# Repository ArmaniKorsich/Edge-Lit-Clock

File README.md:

# Edge Lit Clock

An Atmega328p powered clock using acryllic panels and ws2812b addressable LEDs as displays.
#

## CAD

All drawings created in Inventor 2016.

The clock consists of 5 seperate displays chained together, with:
* 3
* 10
* 6
* 10
* 6*

panels each. Each panel has a number from 0-9 etched in the following order:  

The off order resembles the old Nixie tube number ordering meant to maximize visiblity of all the digits.

\* *The last display has various symbols instead:*  

## Electronics

The Atmega328p drives the WS2812B leds using the eLite and FastLED libraries.

The Atmega328p reads time from a DS32321 RTC.  

To protect time information against power outages, I selected a DS3231 which accepts backup battery voltage on PIN14 in the event that VCC cuts out.

All circuit boards were constructed on 2 layer PCBs.
The circuit boards were manufactured by JLCPCB and designed using Autodesk Eagle.

### Input

The device takes 9-40VDC input with at least 2A current capacity. The LM2575-5V buck converter transforms the input to 5V with a 3A limit.

The average current draw of the Edge Lit CLock is ~350 mA with an average of 16 WS2812B activated at any moment.

### Operation

To turn the device on, set the 'POWERTOGGLE' piano switch on the bottom right of the PCB to the 'DOWN' position.

To turn the alarm on, set the 'ALARMTOGGLE' piano switch to the 'DOWN' position.

The three potentiometers on the device control the RED, GREEN, and BLUE color channels of the LEDs.

Pressing the Photoresist_Set button will toggle tracking ambient brightness. When set, the device will lower the brightness of its LEDs to 20% in a fully dark room.

### Setting a Timer

To set a timer, press the TIMER+ or TIMER- button until the device displays the appropriate countdown time.

To start the timer, pres the TIMER_SET button. The device will begin counting down from the set time.

For countdowns over 30 minutes, the device will display hours on the 2 left displays, and minutes on the 2 right displays.

When the countdown reaches <30 minutes, the device will display minutes on the 2 left displays, and seconds on the 2 right displays.

When the countdown reaches 0 seconds, a buzzer will beep.

To disable the buzzing, press the SNOOZE button or restart the device.

## Schematics

## Source

This project takes advantage of Arduino's public library system, using 
stdio, FastLED ResponsiveAnalaogRead, EEPROM, Wire, RTCLib
and the provided eLite library for controlling the displays.

ResponsiveAnalogRead: Provides fast and mathematically continuous input values. Minimizes noise in low-cost potentiometers.

stdio: Optional, provides useful debugging information in Arduino IDE.

FastLED: A solution to controlling a large quantity of LEDs rapidly and arbitrarily.

RTClib: Interfaces with the DS3231 Real Time Clock, functions for timekeeping.  

## eLite Library

The eLite library represents the bulk of the content of this project, the clock and physical shape of the project are an example applying this library as my entry to Eisenhower Senior High School's 'Yearly Engineering and Innovation Design Scholarship.'    

`uint8_t defineChain(uint8_t numDisplays,...);`. 
> Inputs(NumDisplays): Number of chained displays in the system.    
> return(chainLength): returns the number of displays in the system.

`void defineLedPerPanel(uint8_t led,...);`. 
> Inputs(led): How many displays there are  
> Inputs(,...): The number of leds per panel in a display, seperated by commas.  
> Tells the system how many LEDs each display has. Useful with physically large plexiglass panels that need more lighting.  
> For a system with 5 displays and 2 leds per panel on each display:  
`void defineLedPerPanel(5, 2, 2, 2, 2, 2)`. 

`void setStandardOrder(uint8_t displayToConfigure);`. 
> inputs(displayToConfigure): Which display to configure. 
> Resets the numercal order of panels in a given display to 0, 1, 2, ... , n. 

`void redefinePanelOrder(uint8_t displayToConfigure, uint8_t quantityPanels,...);`. 
> Inputs(displayToConfigure): Which display to configure   
> Inputs(QuantityPanels): Quantity of panels in display 'DisplayToConfigure'   
> Inputs(,...): The custom order of panels in the display, expects 'QuantityPanels' items, seperated by commas.  

`void drawPanel(uint8_t r, uint8_t g, uint8_t b, uint8_t displayCount, int panelToDraw);`. 
> Inputs(R, G, B): 8-bit integer (0-255), sets the primary color of the displays.     
> Inputs(displayCount): Which display to draw to.  
> Inputs(panelToDraw): The panel to activate in color ##RRGGBB   

`void drawChain(uint8_t r, uint8_t g, uint8_t b, uint8_t lengthOfChain,...);`. 
> Inputs(R, G< B): 8-bit integer (0-255), sets the primary color of the displays.  
> Inputs(lengthOfChain): Number of displays to activate in the chain (0-indexed).  
> inputs(,...): The panel number to activate in each display, seperated by commas.   

`void cycleDisplays(int delayTime, int acceleration, bool direc, uint8_t r, uint8_t g, uint8_t b, uint8_t qtyToCycle,...);`. 
> Inputs(delayTime): Pause between advancing the panels (mS).  
> Inputs(acceleration): Time to decrese delayTime by after each iteration. (mS).  
> Inputs(direc): Cycles forwards (1) or backwards (0).   
> Inputs(R, G, B): 8-bit integer (0-255), sets the primary color of the displays.   
> Inputs(qtyToCycle): Number of displays in the chain to cycle through.   
> Inputs(,...): The index of the displays you wish to cycle through.  
> In a chain of 5 displays, if we wish to cycle the 1st, 3rd, and 4th display:  
`void cycleDisplays(delay, acceleration, forward, R, G, B, 3, 0, 2, 3)`.

`void clearDisplay(uint8_t displayToClear);`
> Inputs(displayToClear): Which display to clear, all panels will be deactivated.  

`void clearChain();`
> Turns off all LEDs in the system, clears all displays.

`uint8_t setChainBrightness(uint8_t brightness);`
> Inputs(brightness): 8-bit integer (0-255), sets the overall opacity (brightness) of the LEDs in FastLED.
> return(brightnessLevel): returns the brightness of the LEDs.

`void randomizeDisplays(int delayTime, int acceleration, int iterations, uint8_t r, uint8_t g, uint8_t b, uint8_t qtyToRandomize, ...);`
> Inputs(delayTime): Pause between iterations in milliseconds (mS).    
> Inputs(acceleration): Time to decrease delayTime by after each iteration. (mS).   
> Inputs(iterations): How many times to activate a random panel on the given displays.    
> Inputs(R, G, B): 8-bit integer (0-255), sets the primary color of the displays.   
> Inputs(qtyToRandomize): Number of displays in the chain to randomize.  
> Inputs(,...): The index of the displays you wish to randomize.  
> If iterations is 1, delay and acceleration aren't important, as the given displays will simply output a random panel. Otherwise, this function provides a simple animation to your chain.

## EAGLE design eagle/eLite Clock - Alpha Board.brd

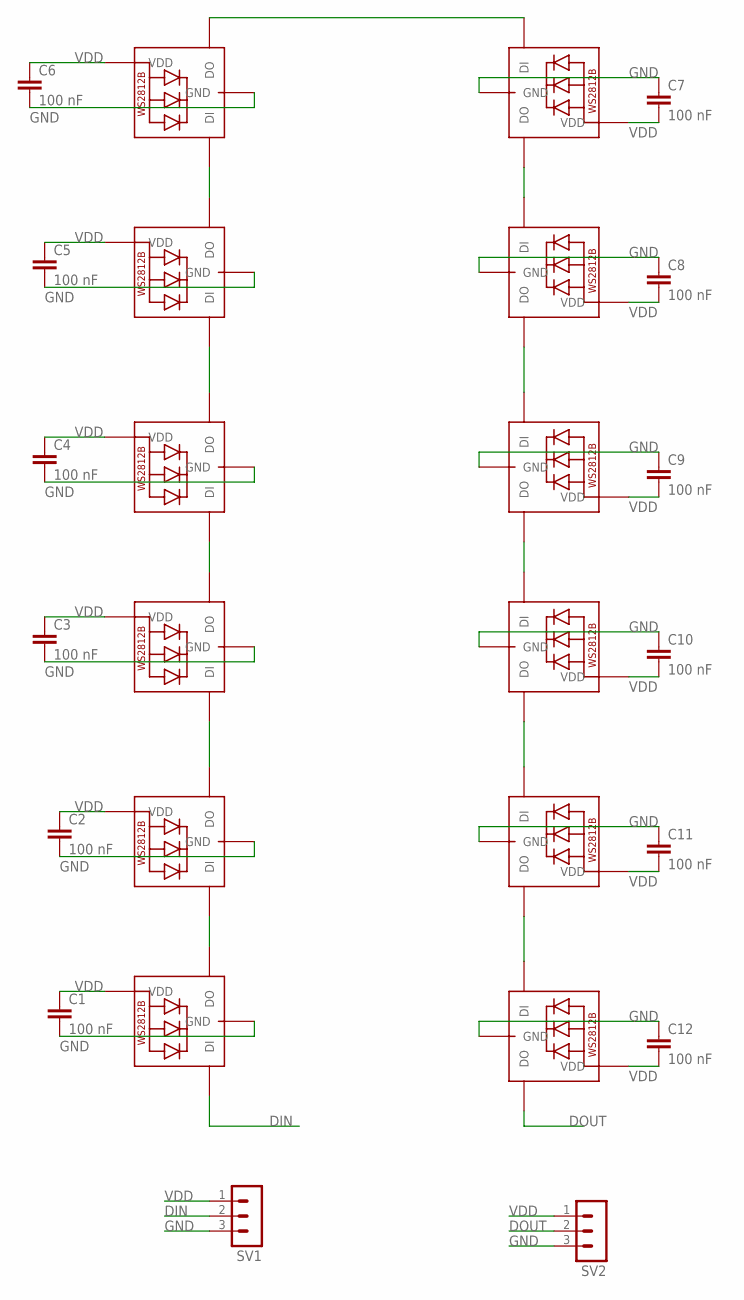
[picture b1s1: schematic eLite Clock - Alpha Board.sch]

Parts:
C1, C2, C3, C4, C5, C6, C7, C8, C9, C10, C11, C12: 100 nF; C025-025X050
LED1, LED2, LED3, LED4, LED5, LED6, LED7, LED8, LED9, LED10, LED11, LED12: WS2812B_5050W; WS2812B-WIDE
SV1, SV2: MA03-1

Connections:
DIN: LED1.4-DIN (DI), SV1.2
DOUT: LED12.2-DOUT (DO), SV2.2
GND: C1.2, C2.2, C3.2, C4.2, C5.2, C6.2, C7.1, C8.1, C9.1, C10.1, C11.1, C12.1, LED1.3-GND (GND), LED2.3-GND (GND), LED3.3-GND (GND), LED4.3-GND (GND), LED5.3-GND (GND), LED6.3-GND (GND), LED7.3-GND (GND), LED8.3-GND (GND), LED9.3-GND (GND), LED10.3-GND (GND), LED11.3-GND (GND), LED12.3-GND (GND), SV1.3, SV2.3
unnamed: LED1.2-DOUT (DO), LED2.4-DIN (DI)
unnamed: LED2.2-DOUT (DO), LED3.4-DIN (DI)
unnamed: LED3.2-DOUT (DO), LED4.4-DIN (DI)
unnamed: LED4.2-DOUT (DO), LED5.4-DIN (DI)
unnamed: LED5.2-DOUT (DO), LED6.4-DIN (DI)
unnamed: LED6.2-DOUT (DO), LED7.4-DIN (DI)
unnamed: LED7.2-DOUT (DO), LED8.4-DIN (DI)
unnamed: LED8.2-DOUT (DO), LED9.4-DIN (DI)
unnamed: LED9.2-DOUT (DO), LED10.4-DIN (DI)
unnamed: LED10.2-DOUT (DO), LED11.4-DIN (DI)
unnamed: LED11.2-DOUT (DO), LED12.4-DIN (DI)
VDD: C1.1, C2.1, C3.1, C4.1, C5.1, C6.1, C7.2, C8.2, C9.2, C10.2, C11.2, C12.2, LED1.1-VDD (VDD), LED2.1-VDD (VDD), LED3.1-VDD (VDD), LED4.1-VDD (VDD), LED5.1-VDD (VDD), LED6.1-VDD (VDD), LED7.1-VDD (VDD), LED8.1-VDD (VDD), LED9.1-VDD (VDD), LED10.1-VDD (VDD), LED11.1-VDD (VDD), LED12.1-VDD (VDD), SV1.1, SV2.1

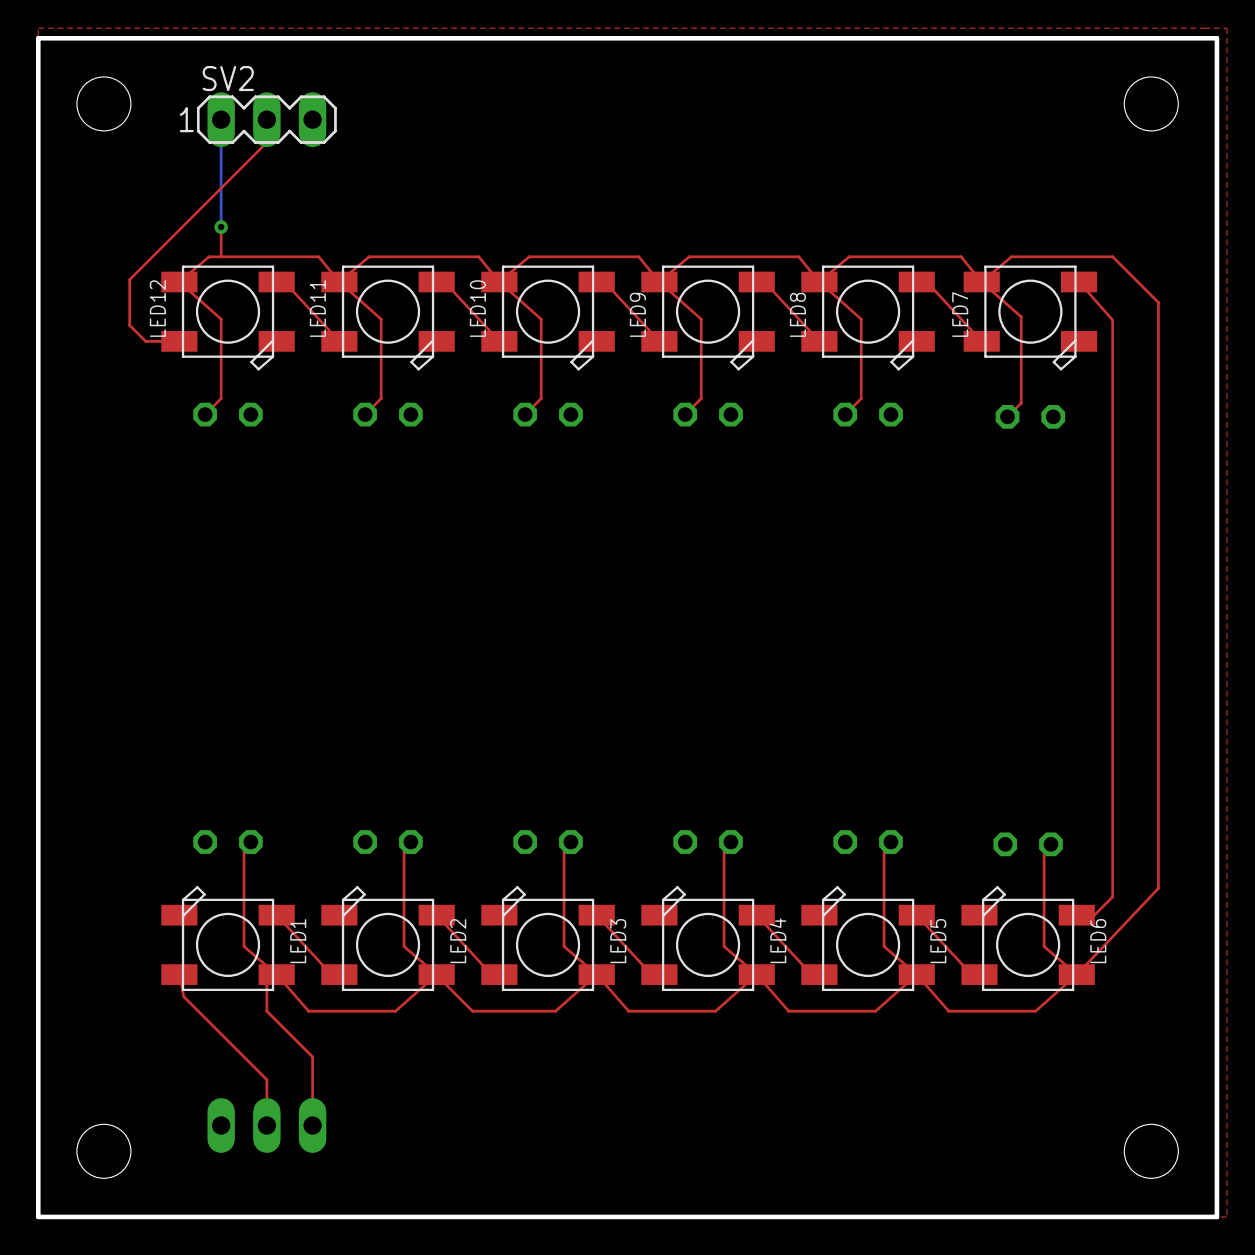
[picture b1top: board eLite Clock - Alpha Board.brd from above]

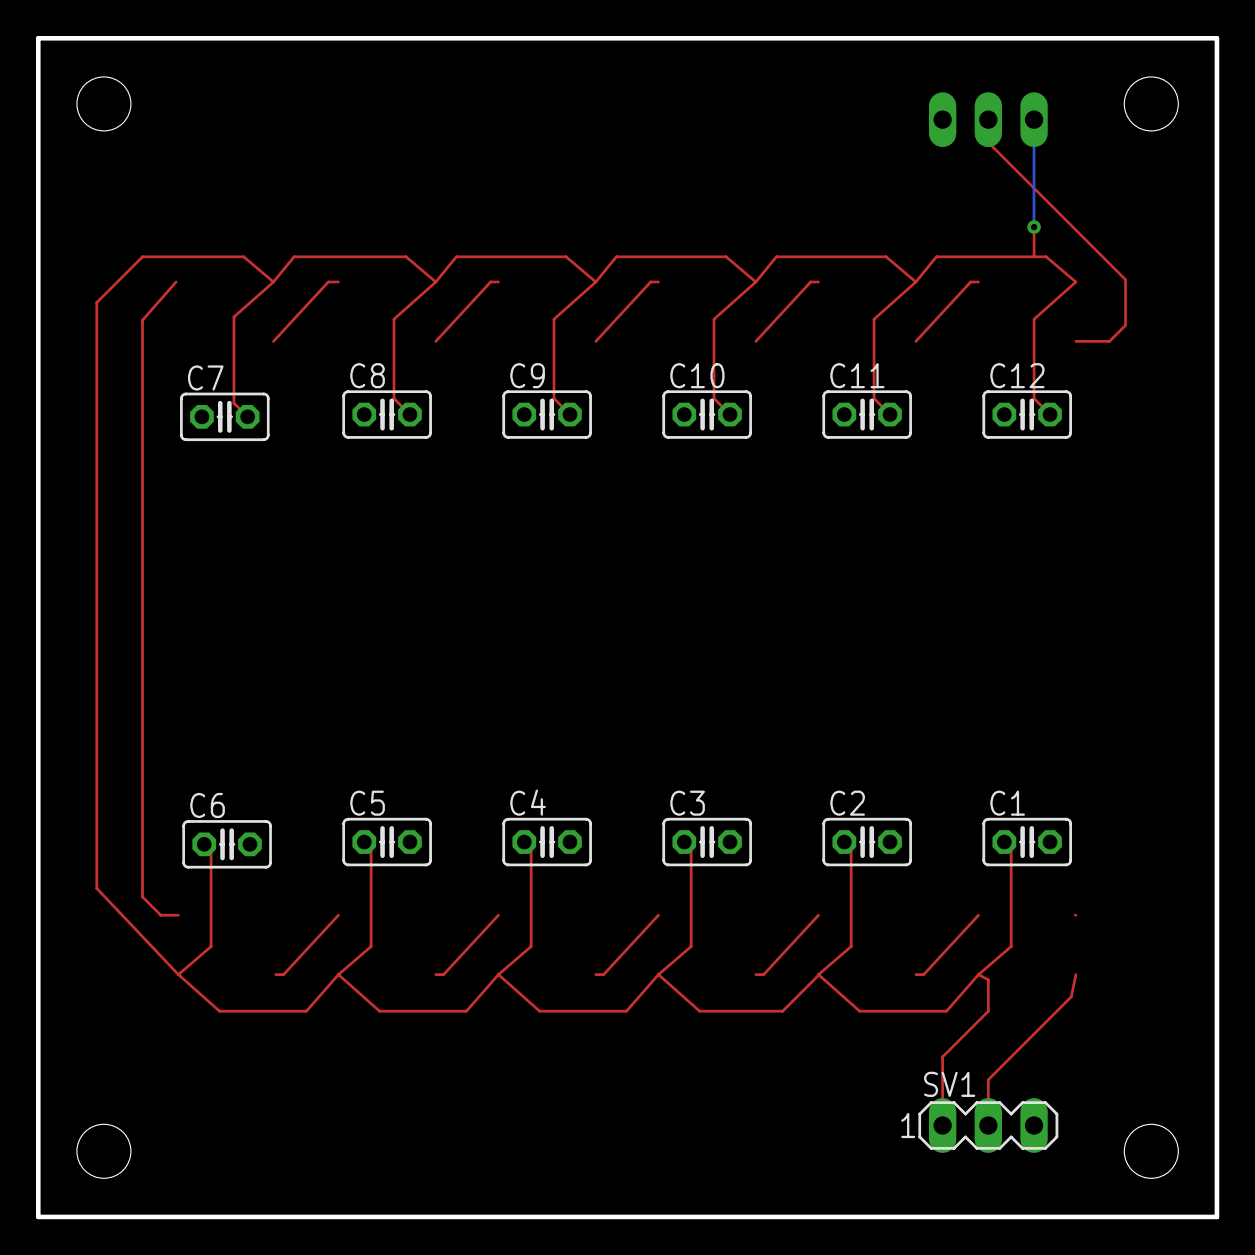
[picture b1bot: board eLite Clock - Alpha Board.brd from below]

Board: 2 copper layers, 65.5 x 65.5 mm, 26 parts (13 on the bottom side), 15 nets.

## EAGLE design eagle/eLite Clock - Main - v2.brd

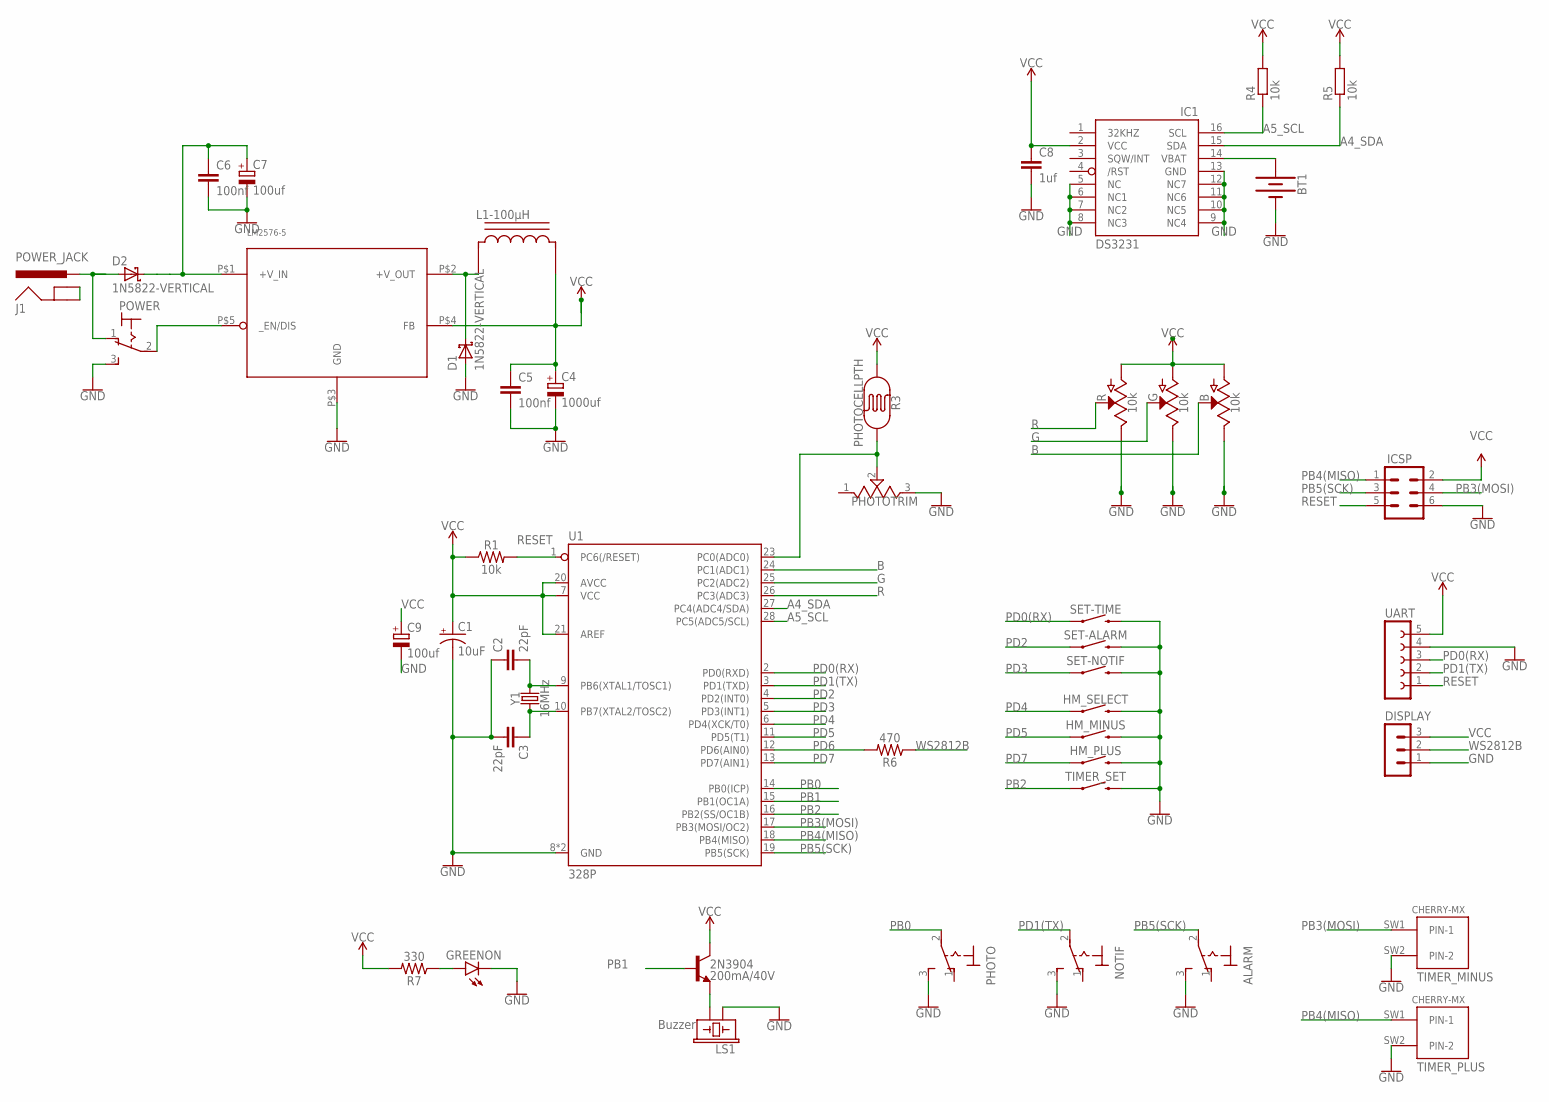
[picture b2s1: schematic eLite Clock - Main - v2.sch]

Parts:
2N3904: 200mA/40V; TO-92
ALARM: 320-916
B: 10k; SINGLE_GANK_POTENTIOMETER
BT1: BATTERY-20MM_PTH; BATTCOM_20MM_PTH
C1: 10uF; CPOL-RADIAL-2.5MM-5MM
C2, C3: 22pF; CAP-PTH-2.54
C4: 1000uf; E5-13
C5, C6: 100nf; C025-025X050
C7: 100uf; E2,5-5
C8: 1uf; C025-025X050
C9: 100uf; E3,5-10
D1, D2: 1N5822-VERTICAL; DIODE-VERTICAL
DISPLAY: MA03-1
G: 10k; SINGLE_GANK_POTENTIOMETER
GREENON: LED5MM
HM_MINUS: MOMENTARY-SWITCH-SPST-PTH-6.0MM; TACTILE_SWITCH_PTH_6.0MM
HM_PLUS: MOMENTARY-SWITCH-SPST-PTH-6.0MM; TACTILE_SWITCH_PTH_6.0MM
HM_SELECT: MOMENTARY-SWITCH-SPST-PTH-6.0MM; TACTILE_SWITCH_PTH_6.0MM
IC1: DS3231/SO; SO16W
ICSP: MA03-2
J1: POWER_JACK; POWER_JACK_PTH
L1-100µH: T37_INDUCTOR
LM2576-5: LM2576-T05A; TO-220-5_IN-LINE
LS1: Buzzer; BUZZER-12MM
NOTIF: 320-916
PHOTO: 320-916
PHOTOTRIM: 3306F-1-203; TRIM_3306F-1-203
POWER: 320-916
R: 10k; SINGLE_GANK_POTENTIOMETER
R1: 10k; AXIAL-0.3
R3: PHOTOCELLPTH; PHOTOCELL
R4, R5: 10k; 0207/7
R6: 470; AXIAL-0.3
R7: 330; AXIAL-0.3
SET-ALARM: MOMENTARY-SWITCH-SPST-PTH-6.0MM; TACTILE_SWITCH_PTH_6.0MM
SET-NOTIF: MOMENTARY-SWITCH-SPST-PTH-6.0MM; TACTILE_SWITCH_PTH_6.0MM
SET-TIME: MOMENTARY-SWITCH-SPST-PTH-6.0MM; TACTILE_SWITCH_PTH_6.0MM
TIMER_MINUS: TIMER_PLUS; CHERRY-MX
TIMER_PLUS: TIMER_MINUS; CHERRY-MX
TIMER_SET: MOMENTARY-SWITCH-SPST-PTH-6.0MM; TACTILE_SWITCH_PTH_6.0MM
U1: 328P; DIP28
UART: FE05-1
Y1: 16MHz; HC49US

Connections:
A4_SDA: IC1.15 (SDA), R5.1, U1.27 (PC4(ADC4/SDA))
A5_SCL: IC1.16 (SCL), R4.1, U1.28 (PC5(ADC5/SCL))
B: B.P$2, U1.24 (PC1(ADC1))
G: G.P$2, U1.25 (PC2(ADC2))
GND: ALARM.3 (S), B.P$1, BT1.2 (-), C1.2 (-), C2.1, C3.2, C4.-, C5.2, C6.2, C7.-, C8.2, C9.-, D1.ANODE (A), DISPLAY.1, G.P$1, GREENON.K (C), HM_MINUS.3 (2), HM_PLUS.3 (2), HM_SELECT.3 (2), IC1.5 (NC), IC1.6 (NC1), IC1.7 (NC2), IC1.8 (NC3), IC1.9 (NC4), IC1.10 (NC5), IC1.11 (NC6), IC1.12 (NC7), IC1.13 (GND), ICSP.6, LM2576-5.P$3 (GND), LS1.+ (1), NOTIF.3 (S), PHOTO.3 (S), PHOTOTRIM.3 (CW), POWER.3 (S), R.P$1, SET-ALARM.3 (2), SET-NOTIF.3 (2), SET-TIME.3 (2), TIMER_MINUS.SW2 (PIN-2), TIMER_PLUS.SW2 (PIN-2), TIMER_SET.3 (2), U1.8 (GND), U1.22 (GND), UART.4
unnamed: J1.GND, J1.GNDBREAK
unnamed: C2.2, U1.9 (PB6(XTAL1/TOSC1)), Y1.2
unnamed: C3.1, U1.10 (PB7(XTAL2/TOSC2)), Y1.1
unnamed: GREENON.A, R7.P$1 (1)
unnamed: PHOTOTRIM.2 (W), R3.2, U1.23 (PC0(ADC0))
unnamed: D2.ANODE (A), J1.PWR, POWER.1 (O)
unnamed: LM2576-5.P$5 (_EN/DIS), POWER.2
unnamed: 2N3904.1 (E), LS1.- (2)
unnamed: D1.CATHODE (C), L1-100µH.CB, LM2576-5.P$2 (+V_OUT)
unnamed: C6.1, C7.+, D2.CATHODE (C), LM2576-5.P$1 (+V_IN)
unnamed: BT1.1 (+), IC1.14 (VBAT)
PB0: PHOTO.2, U1.14 (PB0(ICP))
PB1: 2N3904.2 (B), U1.15 (PB1(OC1A))
PB2: TIMER_SET.1, U1.16 (PB2(SS/OC1B))
PB3(MOSI): ICSP.4, TIMER_MINUS.SW1 (PIN-1), U1.17 (PB3(MOSI/OC2))
PB4(MISO): ICSP.1, TIMER_PLUS.SW1 (PIN-1), U1.18 (PB4(MISO))
PB5(SCK): ALARM.2, ICSP.3, U1.19 (PB5(SCK))
PD0(RX): SET-TIME.1, U1.2 (PD0(RXD)), UART.3
PD1(TX): NOTIF.2, U1.3 (PD1(TXD)), UART.2
PD2: SET-ALARM.1, U1.4 (PD2(INT0))
PD3: SET-NOTIF.1, U1.5 (PD3(INT1))
PD4: HM_SELECT.1, U1.6 (PD4(XCK/T0))
PD5: HM_MINUS.1, U1.11 (PD5(T1))
PD6: R6.P$2 (2), U1.12 (PD6(AIN0))
PD7: HM_PLUS.1, U1.13 (PD7(AIN1))
R: R.P$2, U1.26 (PC3(ADC3))
RESET: ICSP.5, R1.P$2 (2), U1.1 (PC6(/RESET)), UART.1
VCC: 2N3904.3 (C), B.P$3, C1.1 (+), C4.+, C5.1, C8.1, C9.+, DISPLAY.3, G.P$3, IC1.2 (VCC), ICSP.2, L1-100µH.CA, LM2576-5.P$4 (FB), R.P$3, R1.P$1 (1), R3.1, R4.2, R5.2, R7.P$2 (2), U1.7 (VCC), U1.20 (AVCC), U1.21 (AREF), UART.5
WS2812B: DISPLAY.2, R6.P$1 (1)

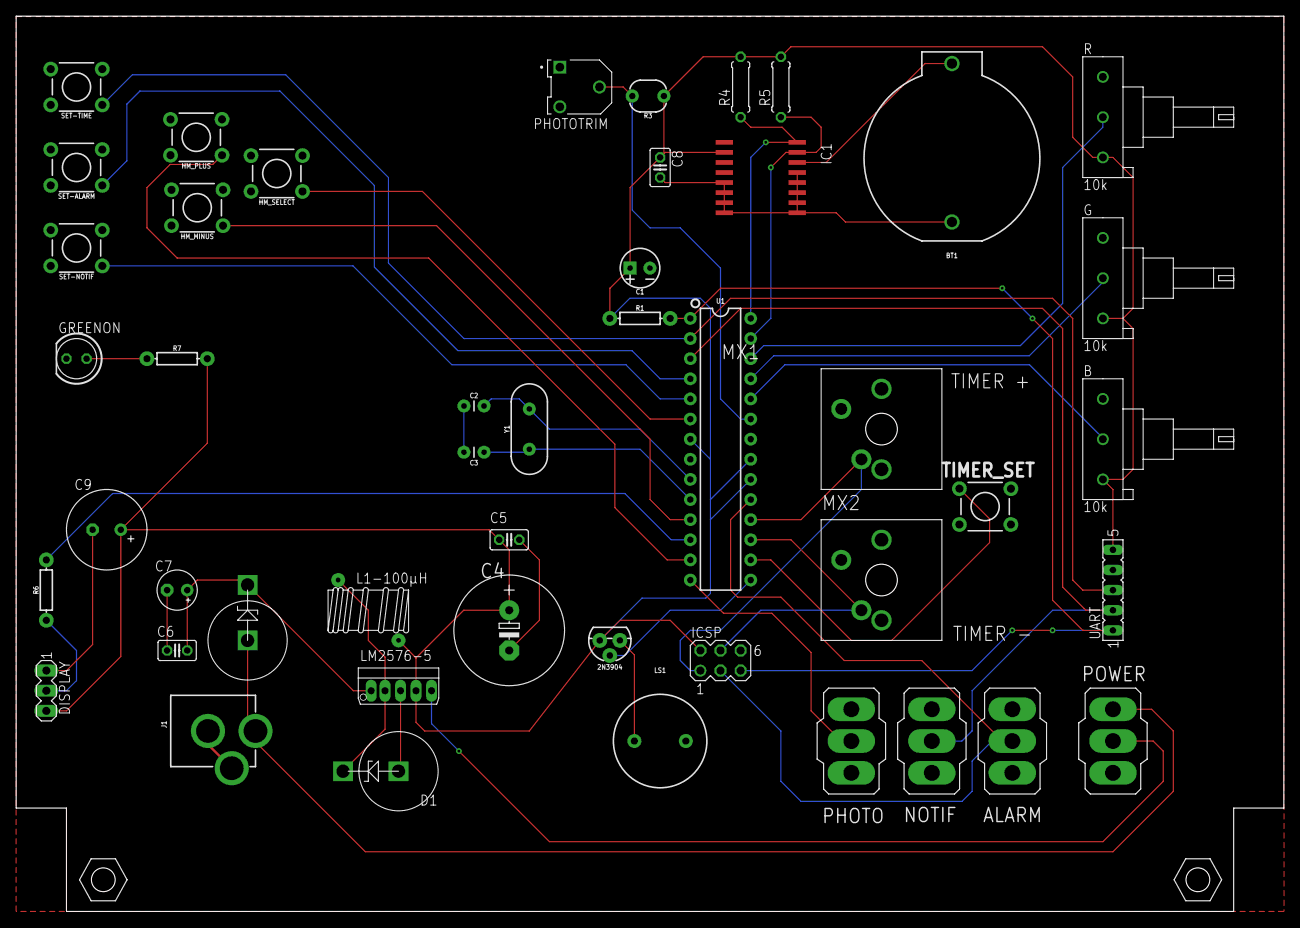
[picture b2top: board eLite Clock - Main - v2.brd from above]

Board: 2 copper layers, 160.0 x 113.0 mm, 47 parts (0 on the bottom side), 34 nets.

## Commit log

2018-10-06 Set theme jekyll-theme-cayman
2018-10-06 Create Images
2018-10-06 Update Images
    create
2018-10-06 Create Images
    create
2018-10-06 Create empty
2020-03-12 Create src
2021-05-28 add device view
2021-05-28 add pcb view
2021-05-28 add ledView
2021-05-28 create eagle folder
2021-05-28 Add files via upload
    This is all the eagle work to generate and view the schematics and circuit boards for this project.

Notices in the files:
parts and their libraries:
SparkFun-Resistors: Licensing: Creative Commons ShareAlike 4.0 International - https://creativecommons.org/licenses/by-sa/4.0
